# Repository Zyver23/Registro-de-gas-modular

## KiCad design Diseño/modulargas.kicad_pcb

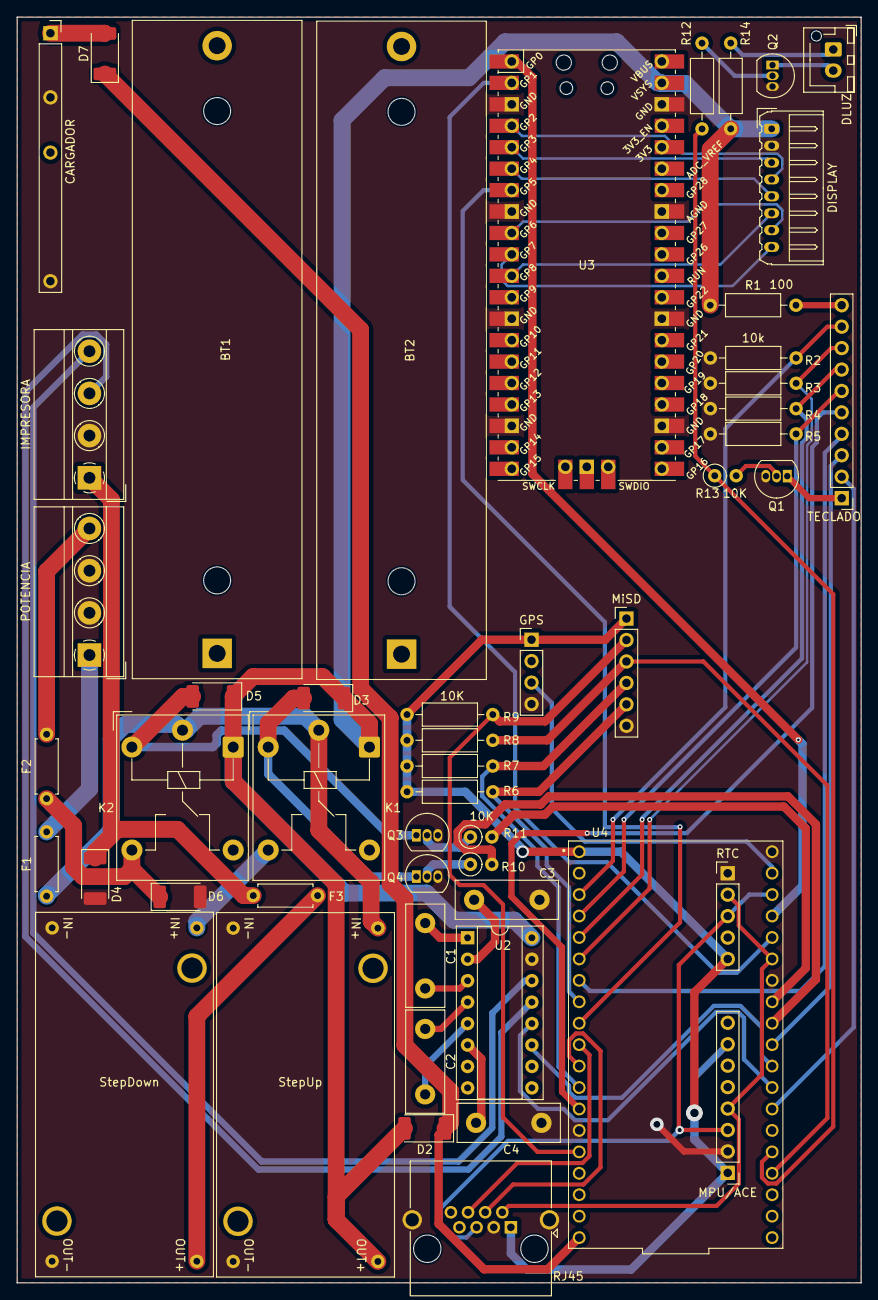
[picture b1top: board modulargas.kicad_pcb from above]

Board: 2 copper layers, 100.0 x 150.0 mm, 52 parts (1 on the bottom side), 62 nets.

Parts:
BT1, BT2: Battery_Cell; BatteryHolder_MPD_BH-18650-PC2
C1, C2, C3, C4: C; C_Disc_D12.0mm_W4.4mm_P7.75mm
CARGADOR: Conversor
D2, D3, D4, D5, D6, D7: SM4001; D_MELF
DISPLAY: DISPLAY; Molex_Micro-Latch_53254-0870_1x08_P2.00mm_Horizontal
DLUZ: DLUZ; JST_XH_B2B-XH-AM_1x02_P2.50mm_Vertical
F1, F2, F3: Fuse_Small; R_Axial_DIN0207_L6.3mm_D2.5mm_P7.62mm_Horizontal
GPS: GPS; PinHeader_1x04_P2.54mm_Vertical
IMPRESORA: IMPRESORA; TerminalBlock_MetzConnect_Type011_RT05504HBWC_1x04_P5.00mm_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
J9: Conn_01x02_Socket; SolderJumper-2_P1.3mm_Bridged_RoundedPad1.0x1.5mm
K1, K2: Fujitsu_FTR-LYCA005x; Relay_SPDT_Hongfa_HF3F-L-xx-1ZL1T
MPU/ACE: ITG; PinHeader_1x08_P2.54mm_Vertical
MiSD: MiSD; PinHeader_1x06_P2.54mm_Vertical
POTENCIA: PONTENCIA; TerminalBlock_MetzConnect_Type011_RT05504HBWC_1x04_P5.00mm_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
Q1, Q2, Q3, Q4: BC548; TO-92_Inline
R1, R14: 100; R_Axial_DIN0207_L6.3mm_D2.5mm_P10.16mm_Horizontal
R2, R3, R4, R5: 10k; R_Axial_DIN0207_L6.3mm_D2.5mm_P10.16mm_Horizontal
R6, R7, R8, R9, R12: 10K; R_Axial_DIN0207_L6.3mm_D2.5mm_P10.16mm_Horizontal
R10, R11, R13: 10K; R_Axial_DIN0207_L6.3mm_D2.5mm_P2.54mm_Vertical
RJ45: RJ45_Shielded; RJ45_Amphenol_RJHSE5380
RTC: DS3231; PinHeader_1x05_P2.54mm_Vertical
StepDown: XL6009-Module
StepUp: XL6009-Module
TECLADO: TECLADO; PinHeader_1x10_P2.54mm_Vertical
U2: MAX232; DIP-16_W7.62mm_Socket
U3: Pico; RPi_Pico_SMD_TH
U4: NODEMCU-32S; MODULE_NODEMCU-32S

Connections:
+3.3V: GPS.1, J9.2, MPU/ACE.1, MiSD.1, R6.2, R7.2, R8.2, R9.2, RJ45.1, RTC.5, U4.J1_1 (3.3V)
+5V: D2.2 (A), D3.1 (K), D5.1 (K), DISPLAY.1, K1.A1, K2.A1, R1.1, R14.1, StepUp.4 (+out), U2.16 (VCC), U3.39 (VSYS)
+12V: F1.1, K1.11, K2.11, StepUp.1 (+in)
/A: RJ45.6, U4.J1_10 (IO26)
/B: RJ45.4, U4.J1_11 (IO27)
/CLK: MiSD.4, R7.1, U4.J1_12 (IO14)
/CS: MiSD.2, R9.1, U4.J1_15 (IO13)
/DBUSY: DISPLAY.8, U3.10 (GPIO7)
/DCMD: DISPLAY.6, U3.11 (GPIO8)
/DCS: DISPLAY.5, U3.6 (GPIO4)
/DMOSI: DISPLAY.3, U3.5 (GPIO3)
/DRST: DISPLAY.7, U3.9 (GPIO6)
/DSCK: DISPLAY.4, U3.4 (GPIO2)
/LUZ: R12.2, R13.1, U4.J2_15 (IO2)
/MISO: MiSD.5, R6.1, U4.J1_8 (IO33)
/MOSI: MiSD.3, R8.1, U4.J2_16 (IO15)
/RPRINT: R10.2, U4.J2_9 (IO18)
/RVALVE: R11.2, U4.J2_8 (IO19)
/SCL: MPU/ACE.3, RJ45.5, RTC.3, U4.J2_3 (IO22)
/SDA: MPU/ACE.4, RJ45.2, RTC.2, U4.J2_6 (IO21)
/c1: R5.1, TECLADO.6, U4.J1_4 (IO39)
/c2: R4.1, TECLADO.7, U4.J1_5 (IO34)
/c3: R3.1, TECLADO.8, U4.J1_6 (IO35)
/c4: R2.1, TECLADO.9, U4.J1_3 (IO36)
/r1: TECLADO.2, U4.J2_13 (IO4)
/r2: TECLADO.3, U4.J2_10 (IO5)
/r3: TECLADO.4, U4.J1_7 (IO32)
/r4: TECLADO.5, U4.J1_13 (IO12)
GND: C3.2, C4.2, CARGADOR.2 (-out), CARGADOR.4 (-in), D4.2 (A), D6.2 (A), DISPLAY.2, GPS.4, IMPRESORA.2, MPU/ACE.2, MiSD.6, POTENCIA.2, POTENCIA.3, Q1.3 (E), Q2.3 (E), Q3.3 (E), Q4.3 (E), R2.2, R3.2, R4.2, R5.2, RJ45.3, RJ45.SH, RTC.1, StepDown.2 (-in), StepDown.3 (-out), StepUp.2 (-in), StepUp.3 (-out), U2.15 (GND), U3.3 (GND), U3.8 (GND), U3.13 (GND), U3.18 (GND), U3.23 (GND), U3.28 (GND), U3.33 (AGND), U3.38 (GND), U4.J1_14 (GND), U4.J2_1 (GND), U4.J2_7 (GND)
unnamed: D2.1 (K), D7.1 (K), U4.J1_19 (5V)
unnamed: D3.2 (A), K1.A2, Q4.1 (C)
unnamed: D4.1 (K), F3.1, IMPRESORA.1
unnamed: D5.2 (A), K2.A2, Q3.1 (C)
unnamed: D6.1 (K), F2.1, K2.14
unnamed: CARGADOR.1 (+out), D7.2 (A)
unnamed: GPS.3, U4.J2_2 (IO23)
unnamed: J9.1, MPU/ACE.7
unnamed: Q1.1 (C), TECLADO.1
unnamed: R1.2, TECLADO.10
unnamed: IMPRESORA.3, U2.13 (R1IN)
unnamed: IMPRESORA.4, U2.14 (T1OUT)
unnamed: F1.2, POTENCIA.1
unnamed: F2.2, POTENCIA.4
unnamed: DLUZ.1, R14.2
unnamed: DLUZ.2, Q2.1 (C)
unnamed: Q1.2 (B), R13.2
unnamed: Q2.2 (B), R12.1
unnamed: Q3.2 (B), R11.1
unnamed: Q4.2 (B), R10.1
unnamed: K1.14, StepDown.1 (+in)
unnamed: F3.2, StepDown.4 (+out)
unnamed: C1.1, U2.1 (C1+)
unnamed: C1.2, U2.3 (C1-)
unnamed: C2.1, U2.4 (C2+)
unnamed: C2.2, U2.5 (C2-)
unnamed: U2.12 (R1OUT), U4.J2_12 (IO16)
unnamed: U2.11 (T1IN), U4.J2_11 (IO17)
unnamed: C3.1, U2.2 (VS+)
unnamed: C4.1, U2.6 (VS-)
unnamed: U3.1 (GPIO0), U4.J2_4 (TX0)
unnamed: U3.2 (GPIO1), U4.J2_5 (RX0)
unnamed: U3.7 (GPIO5), U4.J1_9 (IO25)

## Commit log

2024-09-04 Se agrego el diseño
2024-09-05 Actualization
    Se terminaron de hacer las conexiones
2024-09-17 Arreglo de errores en el dieseño
    Se arreglo la conexion de I2C entre el esp32 y la pico
    Se arrglo la conexion del RTC
    Se conecto lael cargador a los 5v
    Se agrego la conexion para los 5v
    Se agrego el punte para las luces del display
